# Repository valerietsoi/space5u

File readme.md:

Based on ScottoKeeb's stm32f072cbt6 template.

Board untested.

<br>

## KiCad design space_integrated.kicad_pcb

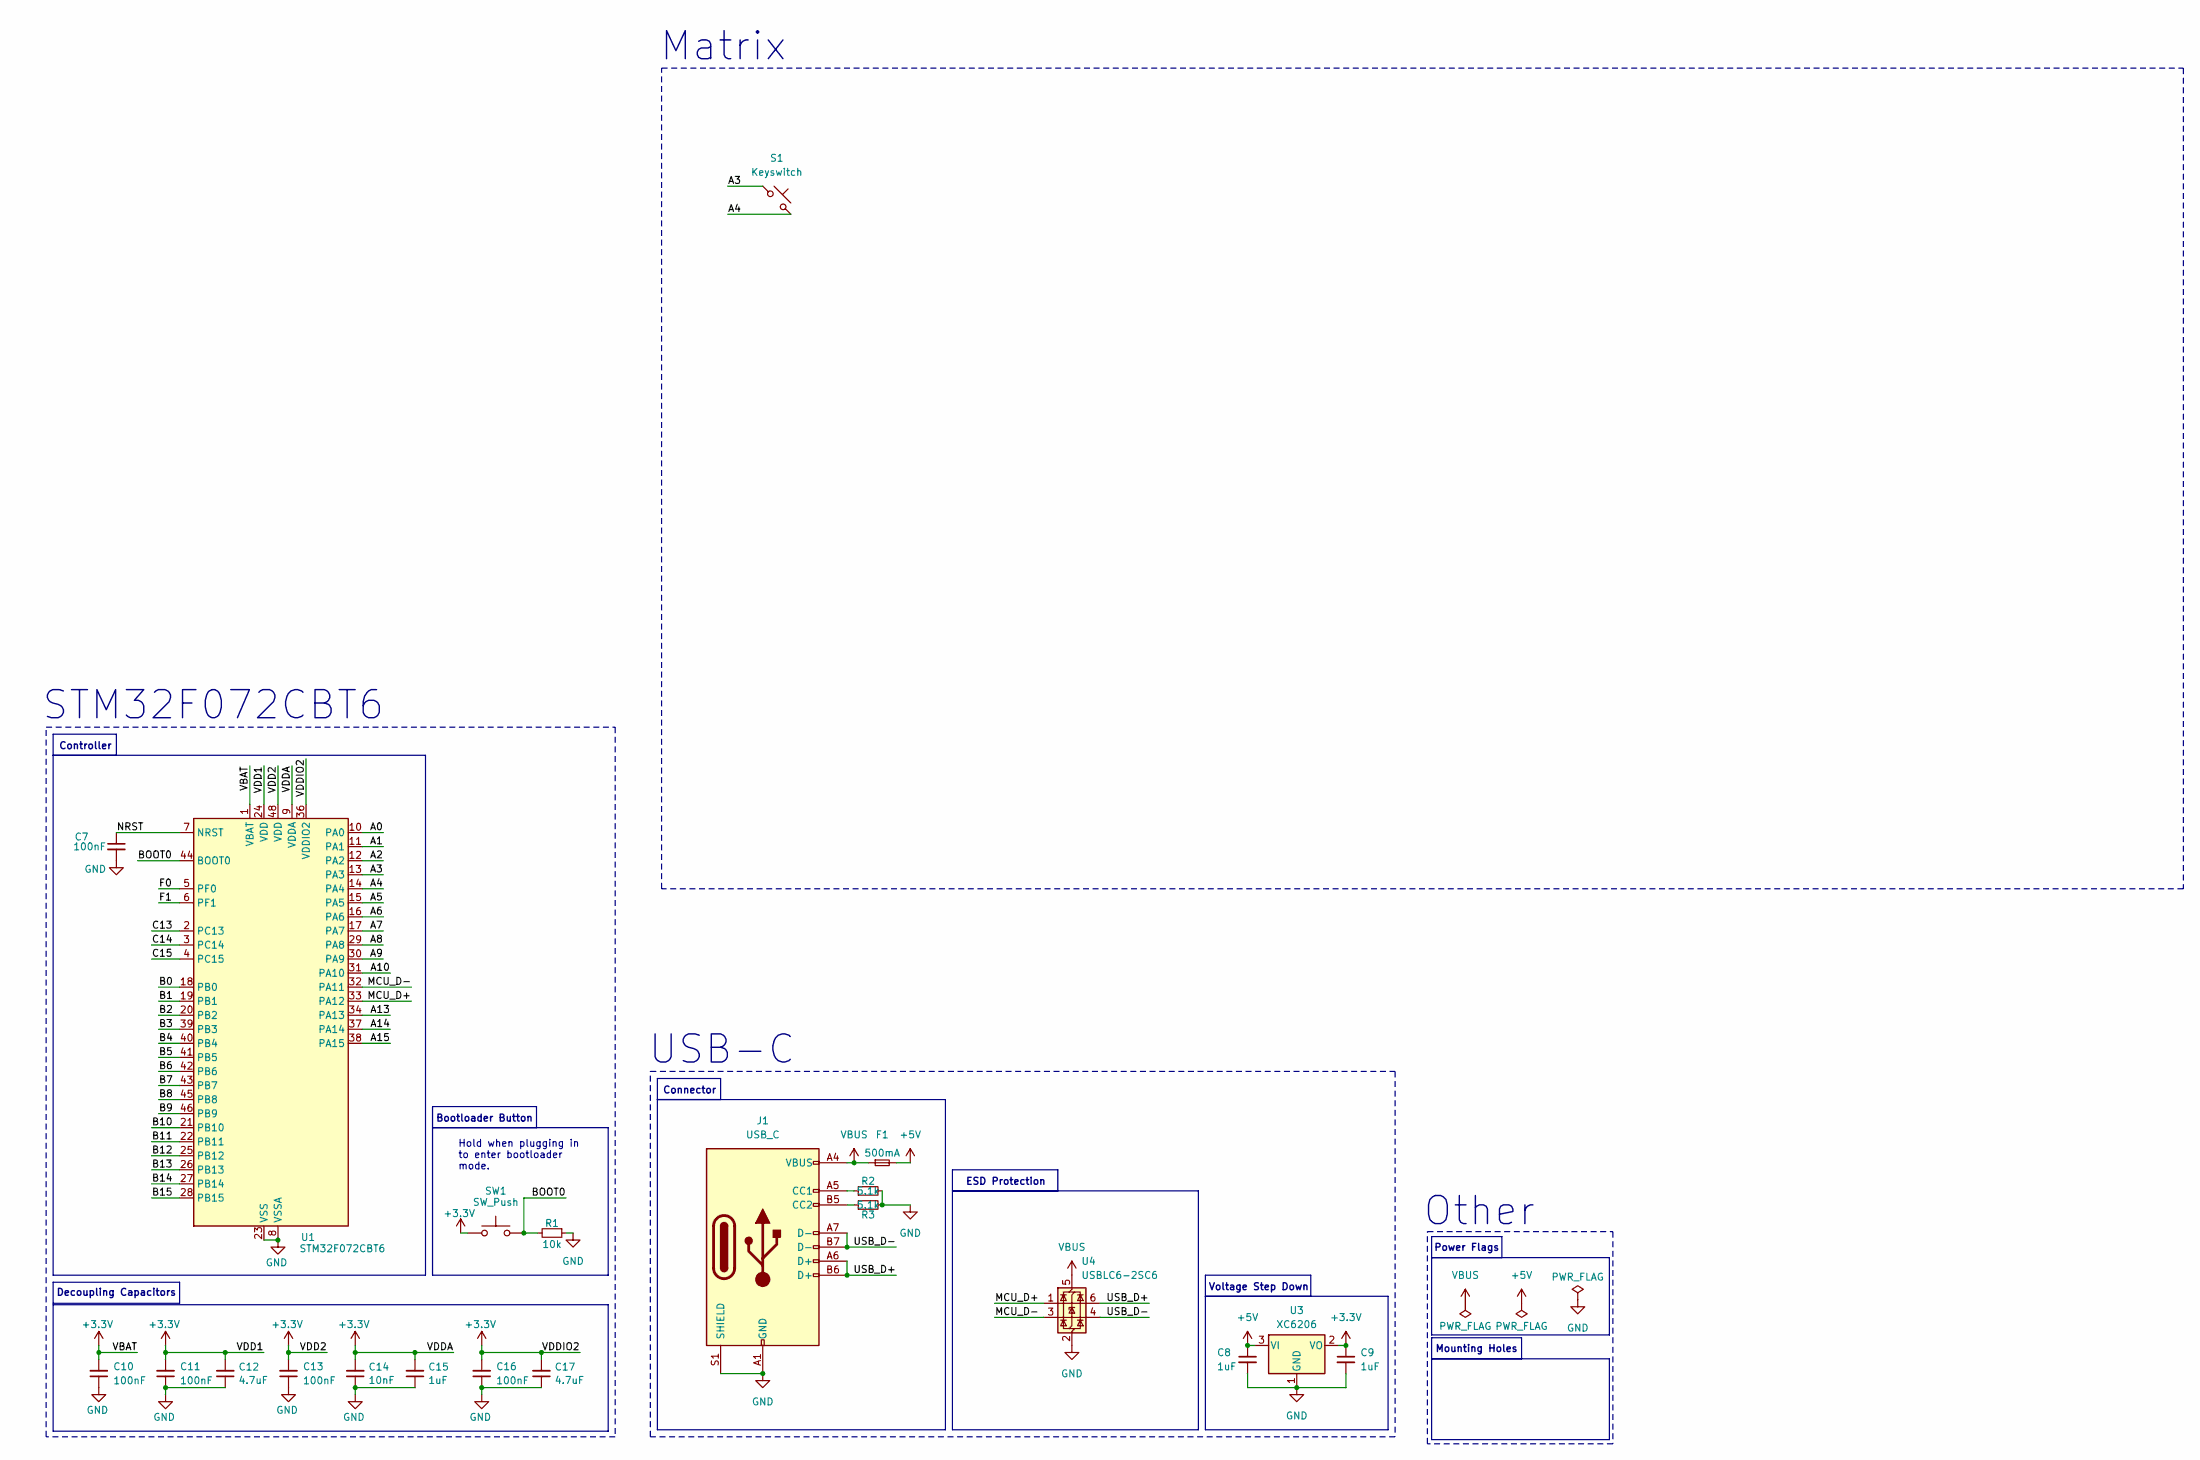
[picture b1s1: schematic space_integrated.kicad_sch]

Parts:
C7: 100nF; Capacitor_0402; LCSC C307331
C8, C9: 1uF; Capacitor_0402; LCSC C52923
C10, C11, C13, C16: 100nF; Capacitor_0402; MPN CL05B104KB54PNC; LCSC C307331
C12, C17: 4.7uF; Capacitor_0402; MPN CL05A475MP5NRNC; LCSC C23733
C14: 10nF; Capacitor_0402; MPN CL05B103KB5NNNC; LCSC C15195
C15: 1uF; Capacitor_0402; MPN CL05A105KA5NQNC; LCSC C52923
F1: 500mA; Fuse_0603; LCSC C210357
J1: USB_C; USB_C_HRO_TYPE-C-31-M-12; LCSC C165948
R1: 10k; Resistor_0402; LCSC C25744
R2, R3: 5.1k; Resistor_0402; LCSC C25905
S1: Keyswitch; SW_MX_HS_CPG151101S11_1u
SW1: SW_Push; Button_TL3342; LCSC C115351
U1: STM32F072CBT6; Package_LQFP-48_7x7mm_P0.5; LCSC C81720
U3: XC6206; Voltage_SOT-23; LCSC C5446
U4: USBLC6-2SC6; ESD_SOT-23-6; LCSC C2827654

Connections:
+3.3V: C9.1, C10.2, C11.2, C12.2, C13.2, C14.2, C15.2, C16.2, C17.2, SW1.1, U1.1 (VBAT), U1.9 (VDDA), U1.24 (VDD), U1.36 (VDDIO2), U1.48 (VDD), U3.2 (VO)
+5V: C8.1, F1.2, U3.3 (VI)
/A0: U1.10 (PA0)
/A1: U1.11 (PA1)
/A2: U1.12 (PA2)
/A3: S1.1, U1.13 (PA3)
/A4: S1.2, U1.14 (PA4)
/A5: U1.15 (PA5)
/A6: U1.16 (PA6)
/A7: U1.17 (PA7)
/A8: U1.29 (PA8)
/A9: U1.30 (PA9)
/A10: U1.31 (PA10)
/A13: U1.34 (PA13)
/A14: U1.37 (PA14)
/A15: U1.38 (PA15)
/B0: U1.18 (PB0)
/B1: U1.19 (PB1)
/B2: U1.20 (PB2)
/B3: U1.39 (PB3)
/B4: U1.40 (PB4)
/B5: U1.41 (PB5)
/B6: U1.42 (PB6)
/B7: U1.43 (PB7)
/B8: U1.45 (PB8)
/B9: U1.46 (PB9)
/B10: U1.21 (PB10)
/B11: U1.22 (PB11)
/B12: U1.25 (PB12)
/B13: U1.26 (PB13)
/B14: U1.27 (PB14)
/B15: U1.28 (PB15)
/BOOT0: R1.2, SW1.2, U1.44 (BOOT0)
/C13: U1.2 (PC13)
/C14: U1.3 (PC14)
/C15: U1.4 (PC15)
/F0: U1.5 (PF0)
/F1: U1.6 (PF1)
/MCU_D+: U1.33 (PA12), U4.1 (I/O1)
/MCU_D-: U1.32 (PA11), U4.3 (I/O2)
/NRST: C7.1, U1.7 (NRST)
/USB_D+: J1.A6 (D+), J1.B6 (D+), U4.6 (I/O1)
/USB_D-: J1.A7 (D-), J1.B7 (D-), U4.4 (I/O2)
GND: C7.2, C8.2, C9.2, C10.1, C11.1, C12.1, C13.1, C14.1, C15.1, C16.1, C17.1, J1.A1 (GND), J1.A12 (GND), J1.B1 (GND), J1.B12 (GND), J1.S1 (SHIELD), R1.1, R2.2, R3.2, U1.8 (VSSA), U1.23 (VSS), U1.35 (VSS), U1.47 (VSS), U3.1 (GND), U4.2 (GND)
unnamed: J1.A5 (CC1), R2.1
unnamed: J1.B5 (CC2), R3.1
VBUS: F1.1, J1.A4 (VBUS), J1.A9 (VBUS), J1.B4 (VBUS), J1.B9 (VBUS), U4.5 (VBUS)

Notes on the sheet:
Hold when plugging in to enter bootloader mode.
STM32F072CBT6
USB-C
Mounting Holes
Decoupling Capacitors
Controller
ESD Protection
Power Flags
Voltage Step Down
Other
Bootloader Button
Matrix
Connector

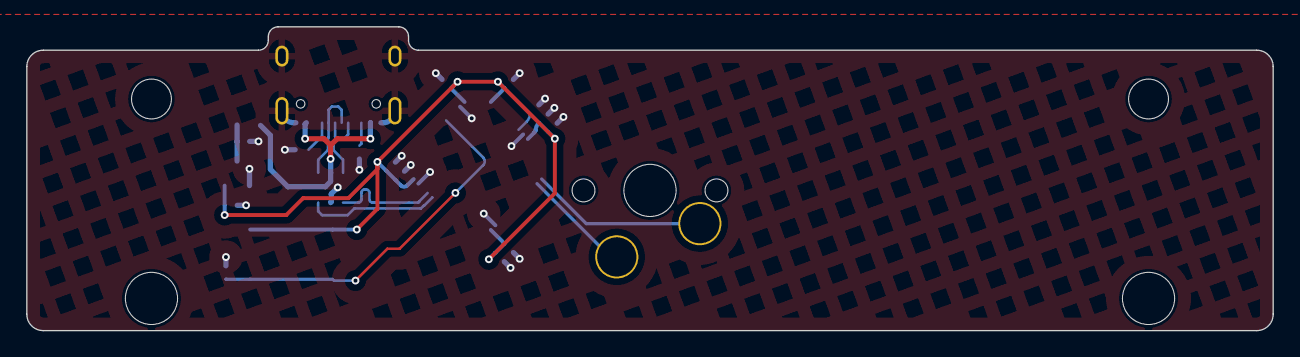
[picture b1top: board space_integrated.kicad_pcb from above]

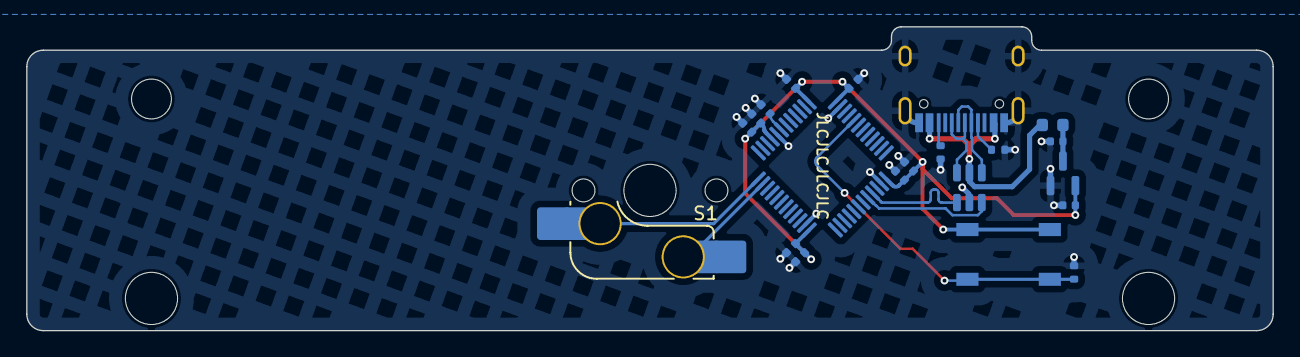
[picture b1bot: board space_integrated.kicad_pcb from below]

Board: 2 copper layers, 95.3 x 23.2 mm, 21 parts (21 on the bottom side), 14 nets.

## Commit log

2025-11-13 kicad files
2025-11-13 readme added
2025-11-13 images
